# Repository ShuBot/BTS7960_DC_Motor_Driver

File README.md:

# BTS7960_DC_Motor_Driver
BTS7960 DC_Motor_Driver

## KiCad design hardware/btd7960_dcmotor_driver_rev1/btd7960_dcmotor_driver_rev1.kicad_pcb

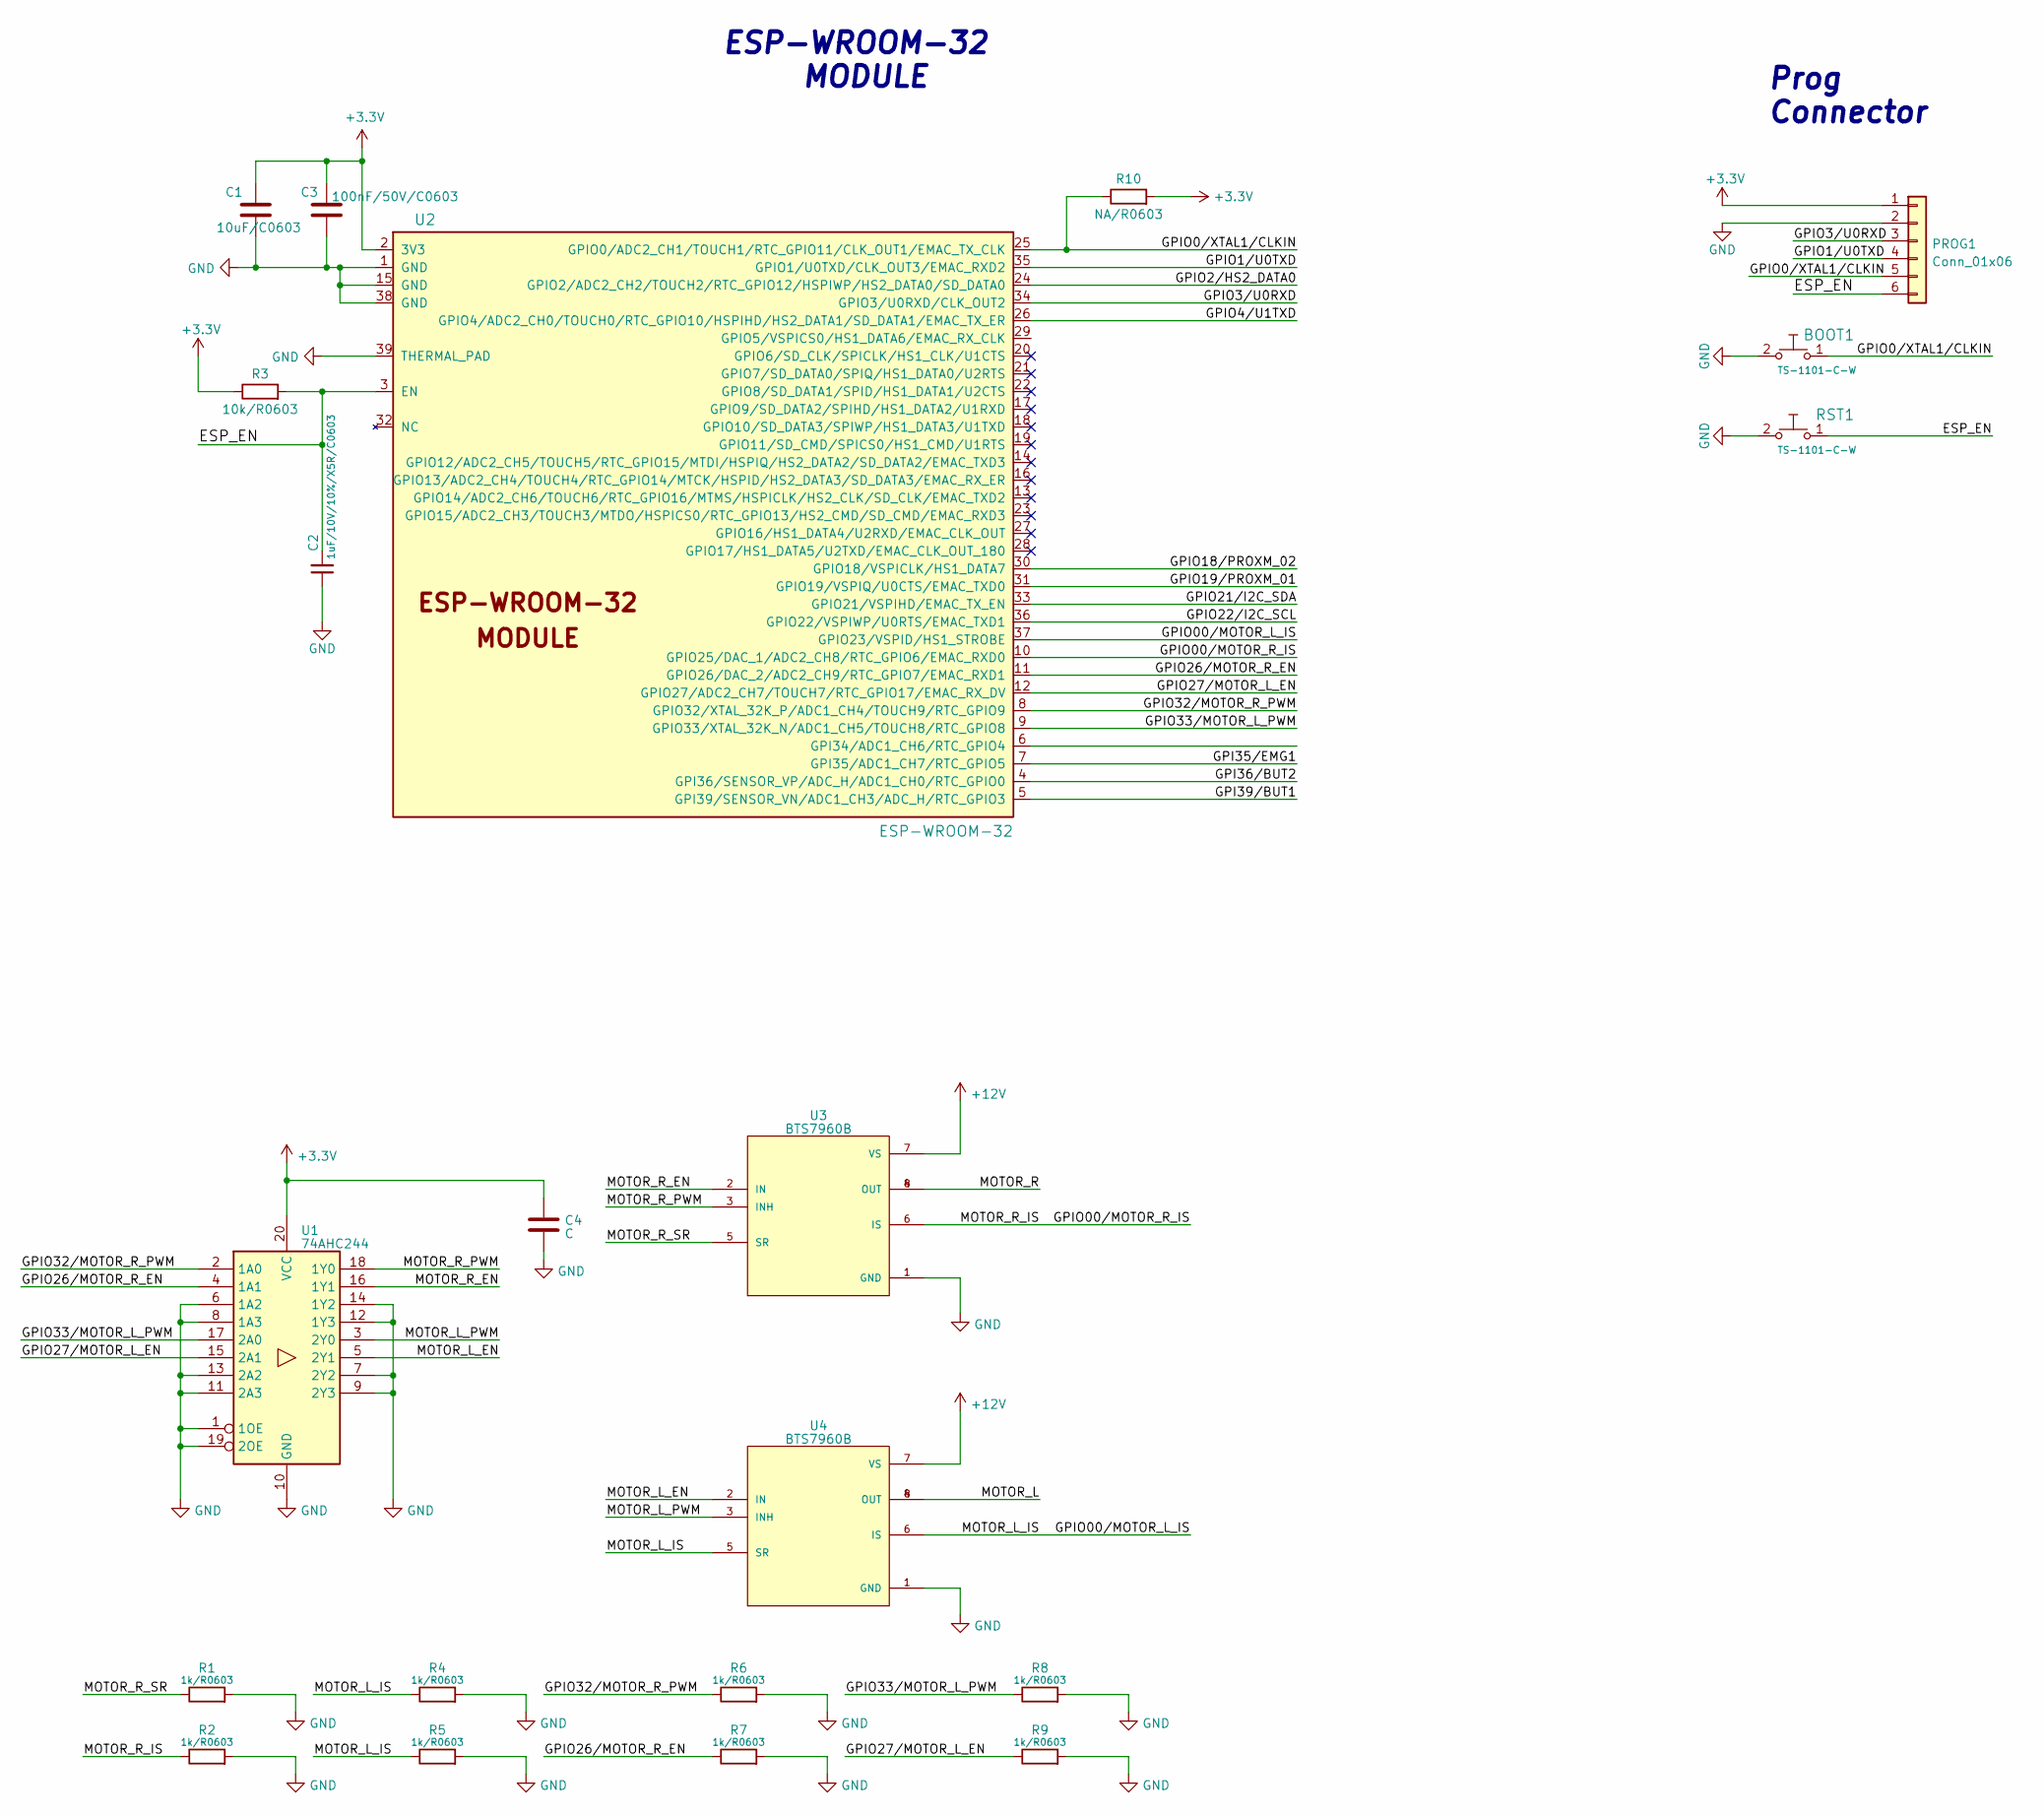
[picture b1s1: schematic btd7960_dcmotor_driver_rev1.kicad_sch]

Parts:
BOOT1: TS-1101-C-W; SW_SPST_CK_RS282G05A3; JLCPCB C318938
C1: 10uF/C0603; C_0603_1608Metric
C2: 1uF/10V/10%/X5R/C0603; C_0603_1608Metric
C3: 100nF/50V/C0603; C_0603_1608Metric
C4: C
PROG1: Conn_01x06; PinHeader_1x06_P2.54mm_Vertical
R1, R2, R4, R5, R6, R7, R8, R9: 1k/R0603; R_0603_1608Metric
R3: 10k/R0603; R_0603_1608Metric
R10: NA/R0603; R_0603_1608Metric
RST1: TS-1101-C-W; SW_SPST_CK_RS282G05A3; JLCPCB C318938
U1: 74AHC244; SO-20_12.8x7.5mm_P1.27mm
U2: ESP-WROOM-32; ESP32-WROOM-32; JLCPCB C2934568
U3, U4: BTS7960B; DPAK127P1490X440-8N; PARTREV 1.1

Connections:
+3V3: C1.1, C3.1, PROG1.1, R3.1, R10.2, U1.20 (VCC), U2.2 (3V3)
+12V: U3.7 (VS), U4.7 (VS)
/ESP_EN: C2.2, PROG1.6, R3.2, RST1.1, U2.3 (EN)
/GPI35/EMG1: U2.7 (GPI35/ADC1_CH7/RTC_GPIO5)
/GPI36/BUT2: U2.4 (GPI36/SENSOR_VP/ADC_H/ADC1_CH0/RTC_GPIO0)
/GPI39/BUT1: U2.5 (GPI39/SENSOR_VN/ADC1_CH3/ADC_H/RTC_GPIO3)
/GPIO00/MOTOR_L_IS: R4.1, R5.1, U2.37 (GPIO23/VSPID/HS1_STROBE), U4.5 (SR), U4.6 (IS)
/GPIO00/MOTOR_R_IS: R2.1, U2.10 (GPIO25/DAC_1/ADC2_CH8/RTC_GPIO6/EMAC_RX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), U3.6 (IS)
/GPIO0/XTAL1/CLKIN: BOOT1.1, PROG1.5, R10.1, U2.25 (GPIO0/ADC2_CH1/TOUCH1/RTC_GPIO11/CLK_OU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)
/GPIO1/U0TXD: PROG1.4, U2.35 (GPIO1/U0TXD/CLK_OUT3/EMAC_RXD2)
/GPIO2/HS2_DATA0: U2.24 (GPIO2/ADC2_CH2/TOUCH2/RTC_GPIO12/HSPIWP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)
/GPIO3/U0RXD: PROG1.3, U2.34 (GPIO3/U0RXD/CLK_OUT2)
/GPIO4/U1TXD: U2.26 (GPIO4/ADC2_CH0/TOUCH0/RTC_GPIO10/HSPIHD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)
/GPIO18/PROXM_02: U2.30 (GPIO18/VSPICLK/HS1_DATA7)
/GPIO19/PROXM_01: U2.31 (GPIO19/VSPIQ/U0CTS/EMAC_TXD0)
/GPIO21/I2C_SDA: U2.33 (GPIO21/VSPIHD/EMAC_TX_EN)
/GPIO22/I2C_SCL: U2.36 (GPIO22/VSPIWP/U0RTS/EMAC_TXD1)
/GPIO26/MOTOR_R_EN: R7.1, U1.4 (1A1), U2.11 (GPIO26/DAC_2/ADC2_CH9/RTC_GPIO7/EMAC_RX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)
/GPIO27/MOTOR_L_EN: R9.1, U1.15 (2A1), U2.12 (GPIO27/ADC2_CH7/TOUCH7/RTC_GPIO17/EMAC_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)
/GPIO32/MOTOR_R_PWM: R6.1, U1.2 (1A0), U2.8 (GPIO32/XTAL_32K_P/ADC1_CH4/TOUCH9/RTC_G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)
/GPIO33/MOTOR_L_PWM: R8.1, U1.17 (2A0), U2.9 (GPIO33/XTAL_32K_N/ADC1_CH5/TOUCH8/RTC_G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)
/MOTOR_L: U4.4 (OUT), U4.8 (OUT)
/MOTOR_L_EN: U1.5 (2Y1), U4.2 (IN)
/MOTOR_L_PWM: U1.3 (2Y0), U4.3 (INH)
/MOTOR_R: U3.4 (OUT), U3.8 (OUT)
/MOTOR_R_EN: U1.16 (1Y1), U3.2 (IN)
/MOTOR_R_PWM: U1.18 (1Y0), U3.3 (INH)
/MOTOR_R_SR: R1.1, U3.5 (SR)
GND: BOOT1.2, C1.2, C2.1, C3.2, PROG1.2, R1.2, R2.2, R4.2, R5.2, R6.2, R7.2, R8.2, R9.2, RST1.2, U1.1 (1OE), U1.6 (1A2), U1.7 (2Y2), U1.8 (1A3), U1.9 (2Y3), U1.10 (GND), U1.11 (2A3), U1.12 (1Y3), U1.13 (2A2), U1.14 (1Y2), U1.19 (2OE), U2.1 (GND), U2.15 (GND), U2.38 (GND), U2.39 (THERMAL_PAD), U3.1 (GND), U4.1 (GND)

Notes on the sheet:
ESP-WROOM-32 MODULE
Prog Connector

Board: 2 copper layers, 20 parts (0 on the bottom side), 20 nets, no tracks yet.

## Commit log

2023-05-02 project initiated
